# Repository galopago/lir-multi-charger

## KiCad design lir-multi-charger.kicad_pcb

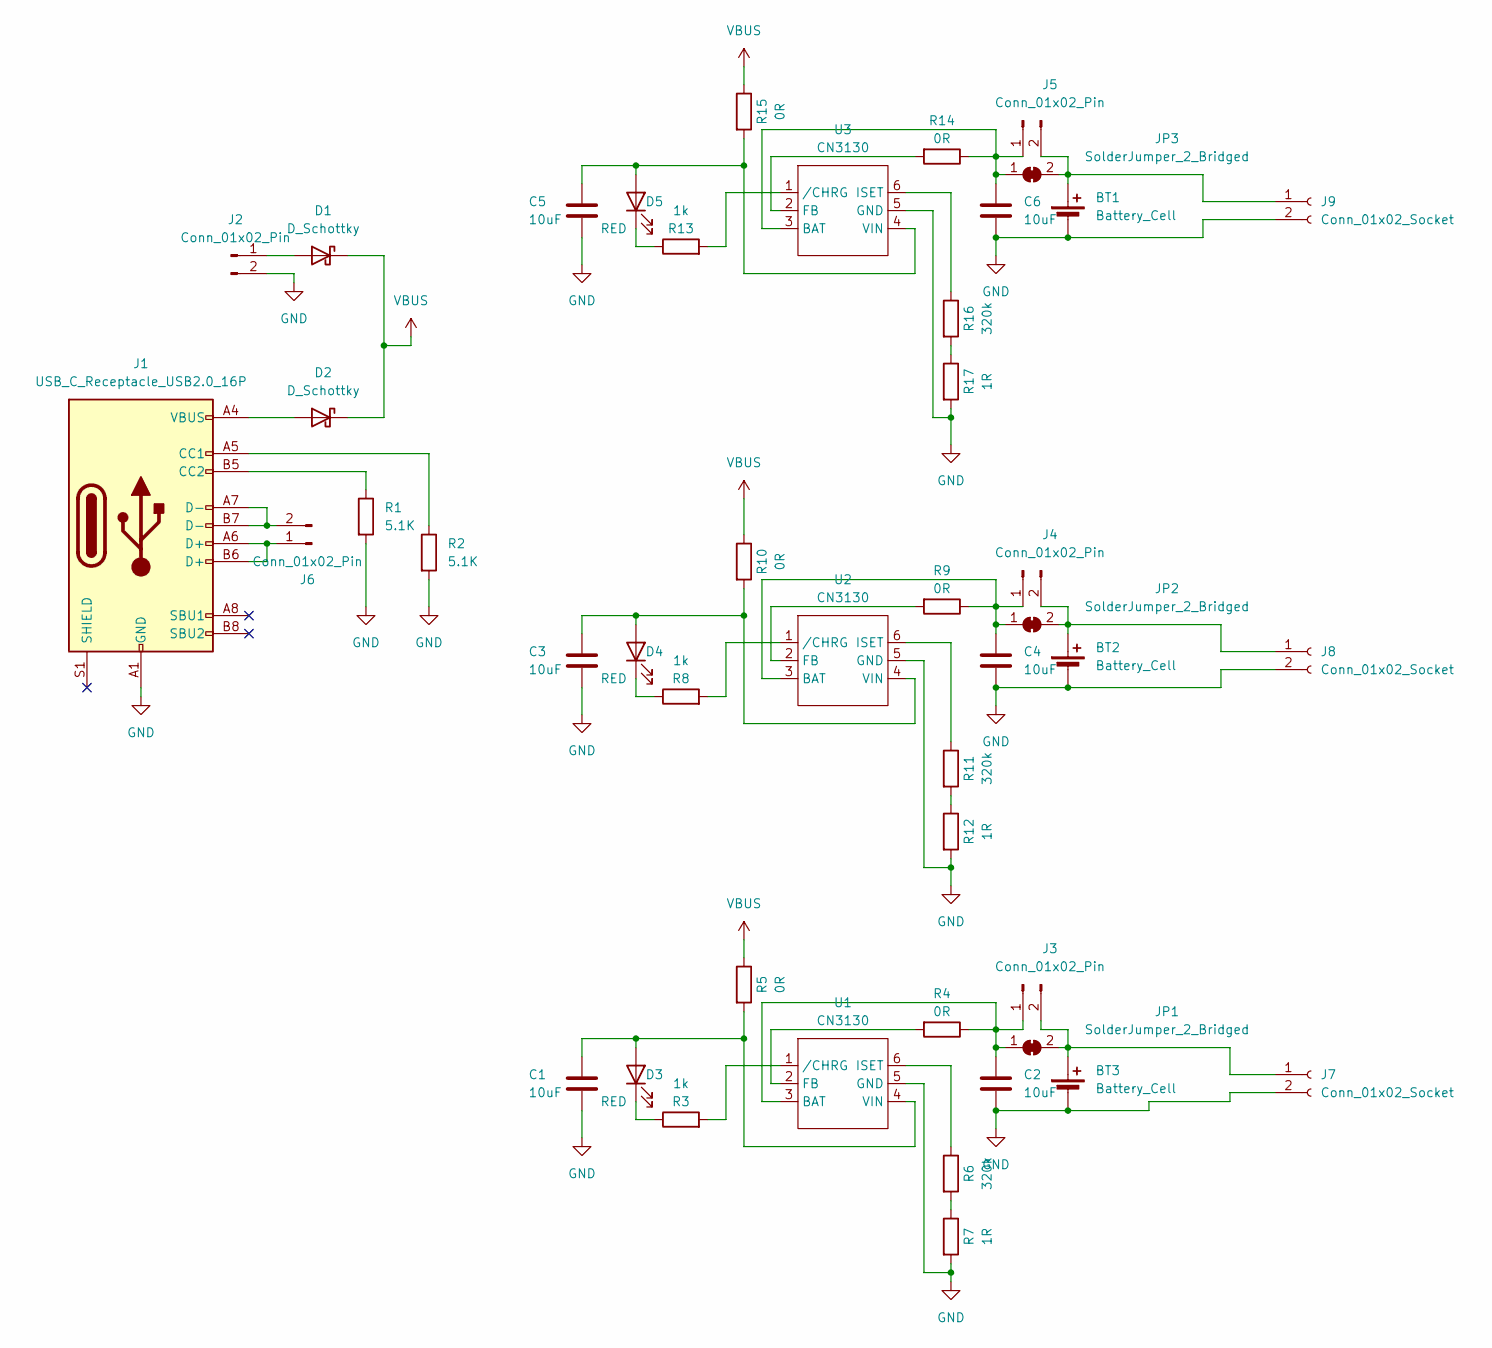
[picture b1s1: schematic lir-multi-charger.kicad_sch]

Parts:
BT1: Battery_Cell; CR2450
BT2: Battery_Cell; CR2032
BT3: Battery_Cell; CR1220
C1, C2, C3, C4, C5, C6: 10uF; C_0805_2012Metric_Pad1.18x1.45mm_HandSolder
D1, D2: D_Schottky; D_SOD-123
D3, D4, D5: RED; LED_0805_2012Metric_Pad1.15x1.40mm_HandSolder
J1: USB_C_Receptacle_USB2.0_16P; USB_C_Receptacle_HRO_TYPE-C-31-M-12
J2, J3, J4, J5, J6: Conn_01x02_Pin; PinHeader_1x02_P2.54mm_Vertical
J7, J8, J9: Conn_01x02_Socket; TerminalBlock_4Ucon_1x02_P3.50mm_Horizontal
JP1, JP2, JP3: SolderJumper_2_Bridged; SolderJumper-2_P1.3mm_Bridged_RoundedPad1.0x1.5mm
R1, R2: 5.1K; R_0805_2012Metric_Pad1.20x1.40mm_HandSolder
R3, R8, R13: 1k; R_0805_2012Metric_Pad1.20x1.40mm_HandSolder
R4, R5, R9, R10, R14, R15: 0R; R_0805_2012Metric_Pad1.20x1.40mm_HandSolder
R6, R11, R16: 320k; R_0805_2012Metric_Pad1.20x1.40mm_HandSolder
R7, R12, R17: 1R; R_0805_2012Metric_Pad1.20x1.40mm_HandSolder
U1, U2, U3: CN3130; SOT-23-6_Handsoldering

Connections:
GND: BT1.2 (-), BT2.2 (-), BT3.2 (-), C1.2, C2.2, C3.2, C4.2, C5.2, C6.2, J1.A1 (GND), J1.A12 (GND), J1.B1 (GND), J1.B12 (GND), J2.2, J7.2, J8.2, J9.2, R1.2, R2.2, R7.2, R12.2, R17.2, U1.5 (GND), U2.5 (GND), U3.5 (GND)
unnamed: BT1.1 (+), J5.2, J9.1, JP3.2 (B)
unnamed: BT2.1 (+), J4.2, J8.1, JP2.2 (B)
unnamed: BT3.1 (+), J3.2, J7.1, JP1.2 (B)
unnamed: D1.2 (A), J2.1
unnamed: D2.2 (A), J1.A4 (VBUS), J1.A9 (VBUS), J1.B4 (VBUS), J1.B9 (VBUS)
unnamed: C1.1, D3.2 (A), R5.2, U1.4 (VIN)
unnamed: D3.1 (K), R3.1
unnamed: C3.1, D4.2 (A), R10.2, U2.4 (VIN)
unnamed: D4.1 (K), R8.1
unnamed: C5.1, D5.2 (A), R15.2, U3.4 (VIN)
unnamed: D5.1 (K), R13.1
unnamed: J1.A5 (CC1), R2.1
unnamed: J1.B5 (CC2), R1.1
unnamed: C2.1, J3.1, JP1.1 (A), R4.1, U1.3 (BAT)
unnamed: C4.1, J4.1, JP2.1 (A), R9.1, U2.3 (BAT)
unnamed: C6.1, J5.1, JP3.1 (A), R14.1, U3.3 (BAT)
unnamed: J1.A6 (D+), J1.B6 (D+), J6.1
unnamed: J1.A7 (D-), J1.B7 (D-), J6.2
unnamed: R6.2, R7.1
unnamed: R11.2, R12.1
unnamed: R16.2, R17.1
unnamed: R4.2, U1.2 (FB)
unnamed: R6.1, U1.6 (ISET)
unnamed: R3.2, U1.1 (/CHRG)
unnamed: R9.2, U2.2 (FB)
unnamed: R11.1, U2.6 (ISET)
unnamed: R8.2, U2.1 (/CHRG)
unnamed: R14.2, U3.2 (FB)
unnamed: R16.1, U3.6 (ISET)
unnamed: R13.2, U3.1 (/CHRG)
VBUS: D1.1 (K), D2.1 (K), R5.1, R10.1, R15.1

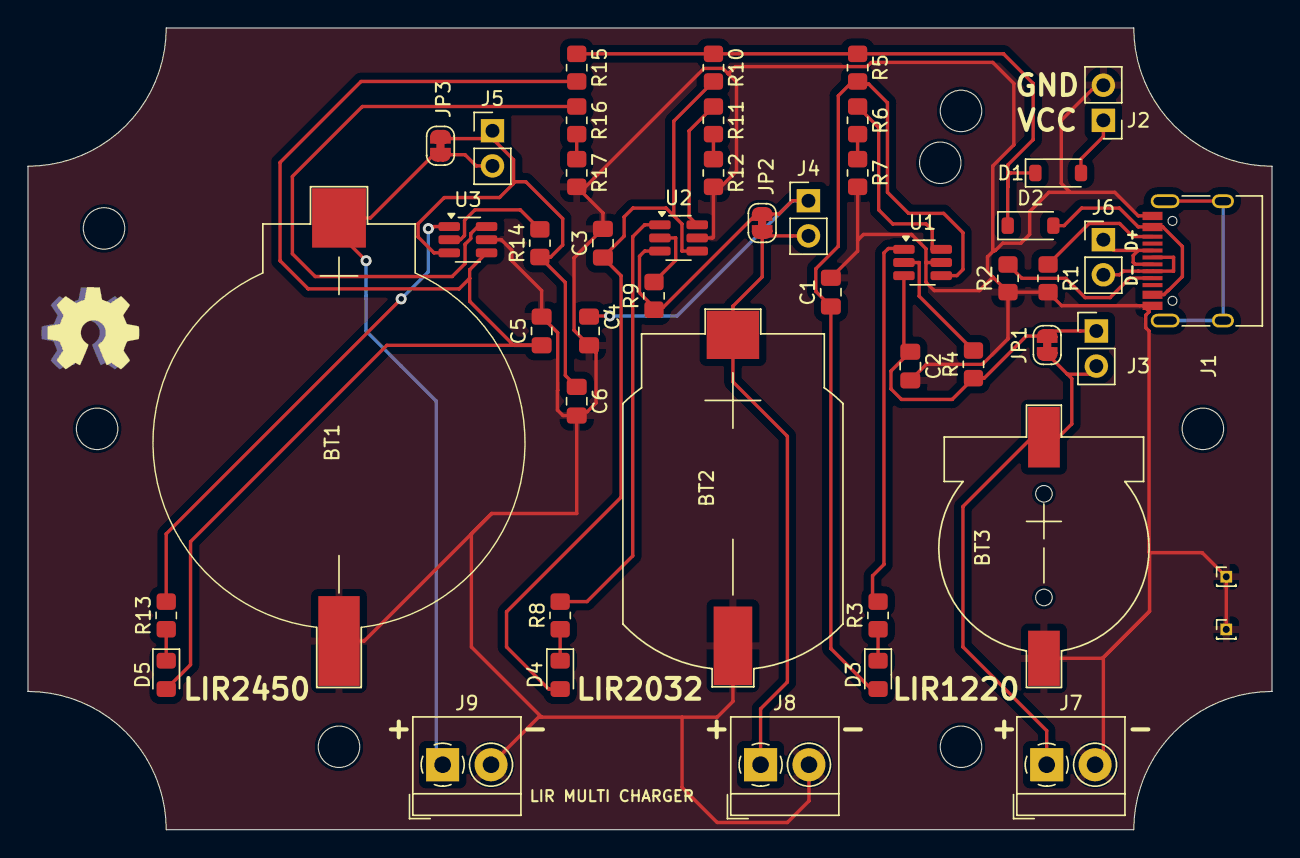
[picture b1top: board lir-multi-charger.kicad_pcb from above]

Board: 2 copper layers, 90.0 x 58.0 mm, 55 parts (1 on the bottom side), 32 nets.

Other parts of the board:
H0, H1, H2, H3, H4, H5, H6: MountingHole; MountingHole_3mm
OSHW1: OSHW-Symbol_6.7x6mm_SilkScreen
OSHW2: OSHW-Symbol_6.7x6mm_Copper

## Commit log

2023-09-21 started project
2023-09-24 finished CR2450 battery holder footprint
2023-09-25 started cr2032
2023-09-26 cr2032 silks done
2023-09-27 finished cr2032
2023-09-28 started cr1220
2023-09-29 finished cr1220
2023-10-03 started charger schematic
2023-10-05 started placing components
2023-10-06 placing components
2023-10-19 all components placed
2023-10-19 board routed
2023-10-19 single gerber
2024-08-11 changed charger IC
2024-08-14 gerbers single
2025-04-02 upgraded kicad version to 9, starting to add ext bat connectors
2025-04-07 Revert "upgraded kicad version to 9, starting to add ext bat connectors"
    This reverts commit a6eeaf41d868e39ea5ead22df93e0c5d5fe9c91a.
2025-09-18 Update PCB design for KiCad 7 compatibility and add external battery connector
    - Migrated project from KiCad 6 to KiCad 7
    - Updated library links and component references for KiCad 7 compatibility
    - Added external battery connector terminal block
    - Updated project files (.kicad_pro, .kicad_prl, .kicad_sch, .kicad_pcb)
    - Updated footprint info cache for new component references
    - Added new backup files from recent design iterations
2025-09-19 Add two screw terminal blocks for external battery connections
    - Added TB1 and TB2 terminal blocks to schematic for external battery charging
    - Routed PCB layout with new terminal block components
    - Connected terminals to power rails for battery input
    - Enables external battery charging capability
2025-10-23 Update PCB design: modify resistor values and add labels for better readability
